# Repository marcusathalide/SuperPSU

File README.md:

This is a replacement power supply unit for the Commodore 64. The unit contains protection elements that shall avoid to damage the C64 during an over-voltage event.

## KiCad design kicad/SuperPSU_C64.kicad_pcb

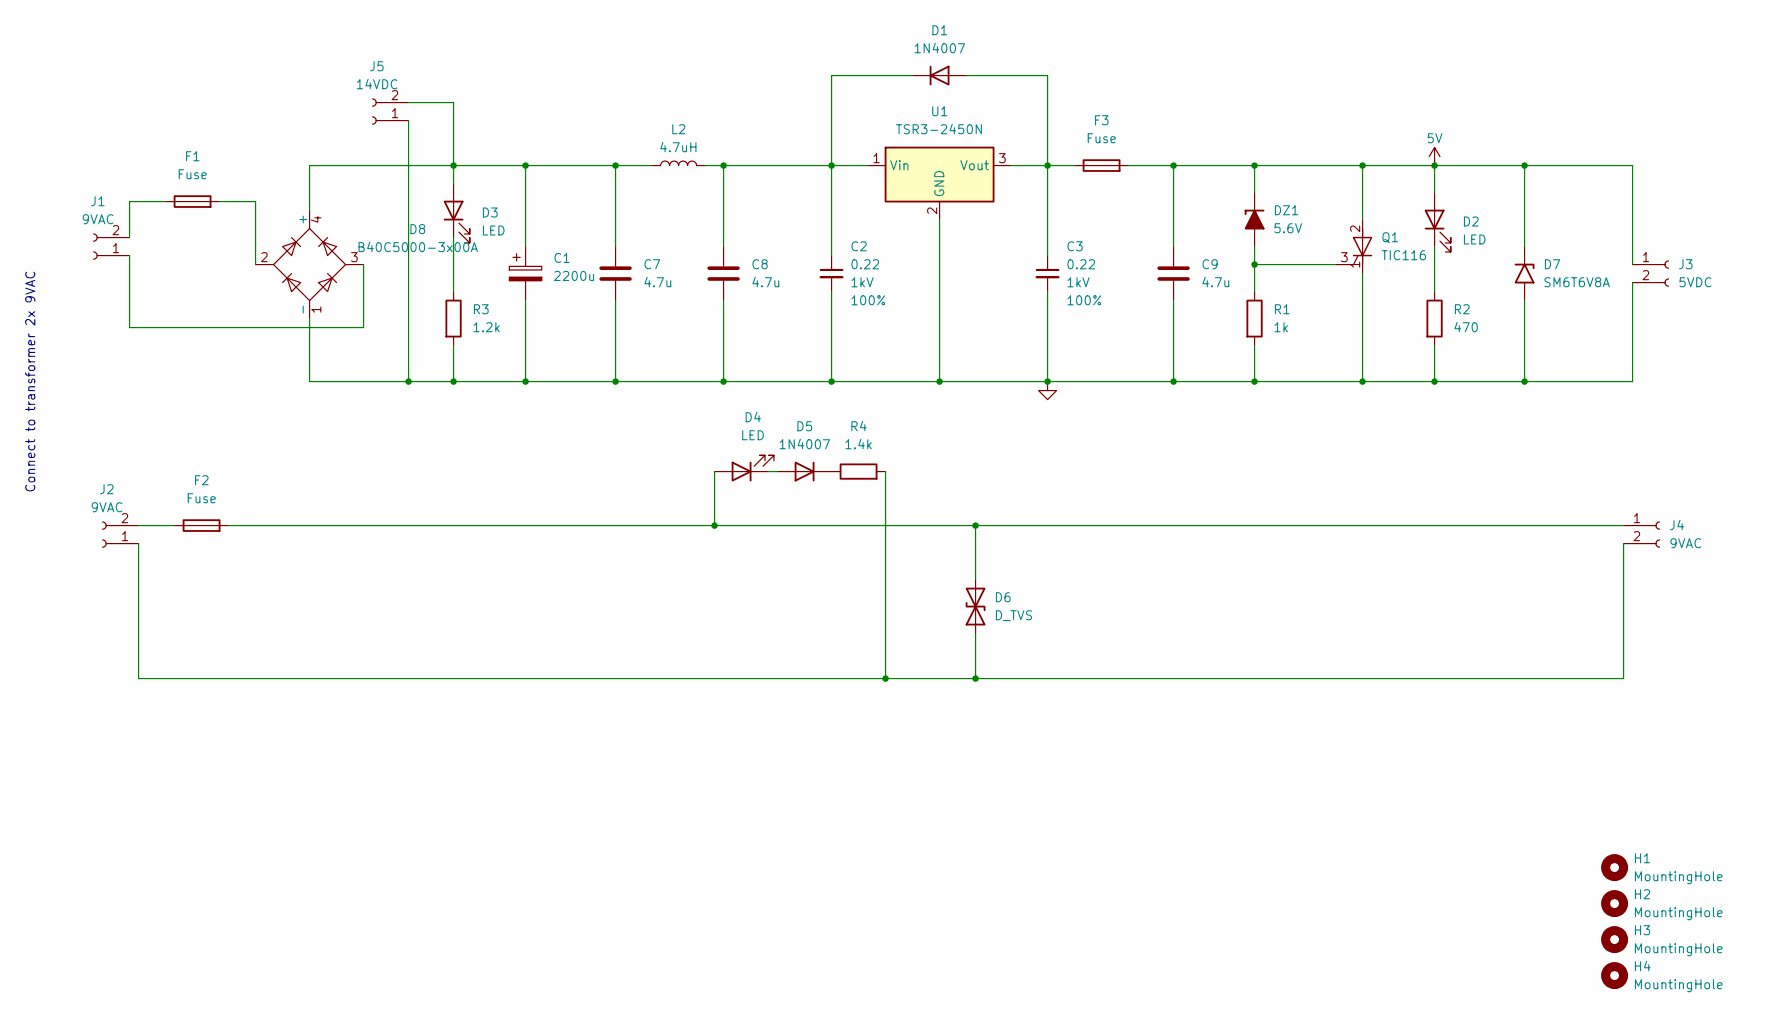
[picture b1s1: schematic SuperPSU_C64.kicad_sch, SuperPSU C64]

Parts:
C1: 2200u; CP_Radial_D16.0mm_P7.50mm
C2, C3: 0.22; C_Disc_D3.0mm_W2.0mm_P2.50mm; Voltage 1kV; Tolerance 100%
C7, C8, C9: 4.7u; CP_Radial_D6.3mm_P2.50mm
D1, D5: 1N4007; D_DO-41_SOD81_P10.16mm_Horizontal
D2, D3, D4: LED; LED_D5.0mm
D6: D_TVS; D_DO-41_SOD81_P10.16mm_Horizontal
D7: SM6T6V8A; D_5W_P10.16mm_Horizontal
D8: B40C5000-3x00A; Diode_Bridge_32.0x5.6x17.0mm_P10.0mm_P7.5mm
DZ1: 5.6V; D_5W_P10.16mm_Horizontal
F1, F2, F3: Fuse; Fuseholder_Littelfuse_445_030_series_5x20mm
H1, H2, H3, H4: MountingHole; MountingHole_3.2mm_M3_DIN965
J1, J2, J4: 9VAC; SolderWire-0.75sqmm_1x02_P7mm_D1.25mm_OD3.5mm
J3: 5VDC; SolderWire-0.75sqmm_1x02_P7mm_D1.25mm_OD3.5mm
J5: 14VDC; SolderWire-0.75sqmm_1x02_P7mm_D1.25mm_OD3.5mm
L2: 4.7uH; L_Bourns_SRP5030T
Q1: TIC116; TO-220-3_Vertical
R1: 1k; R_Axial_DIN0207_L6.3mm_D2.5mm_P10.16mm_Horizontal
R2: 470; R_Axial_DIN0207_L6.3mm_D2.5mm_P10.16mm_Horizontal
R3: 1.2k; R_Axial_DIN0207_L6.3mm_D2.5mm_P10.16mm_Horizontal
R4: 1.4k; R_Axial_DIN0207_L6.3mm_D2.5mm_P10.16mm_Horizontal
U1: TSR3-2450N; Converter_DCDC_TRACO_TSR2-24xxN_TSR2-24xxxN_THT

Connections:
5V: C9.1, D2.2 (A), D7.1 (A1), DZ1.1 (K), F3.2, J3.1, Q1.2 (A)
GND: C1.2, C2.2, C3.2, C7.2, C8.2, C9.2, D7.2 (A2), D8.1 (-), J3.2, J5.1, Q1.1 (K), R1.2, R2.2, R3.2, U1.2 (GND)
unnamed: C3.1, D1.2 (A), F3.1, U1.3 (Vout)
unnamed: C2.1, C8.1, D1.1 (K), L2.2, U1.1 (Vin)
unnamed: D2.1 (K), R2.1
unnamed: C1.1, C7.1, D3.2 (A), D8.4 (+), J5.2, L2.1
unnamed: D3.1 (K), R3.1
unnamed: D4.2 (A), D6.2 (A2), F2.2, J4.1
unnamed: D4.1 (K), D5.2 (A)
unnamed: D5.1 (K), R4.1
unnamed: D6.1 (A1), J2.1, J4.2, R4.2
unnamed: D8.2, F1.2
unnamed: DZ1.2 (A), Q1.3 (G), R1.1
unnamed: D8.3, J1.1
unnamed: F1.1, J1.2
unnamed: F2.1, J2.2

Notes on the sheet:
Connect to transformer 2x 9VAC

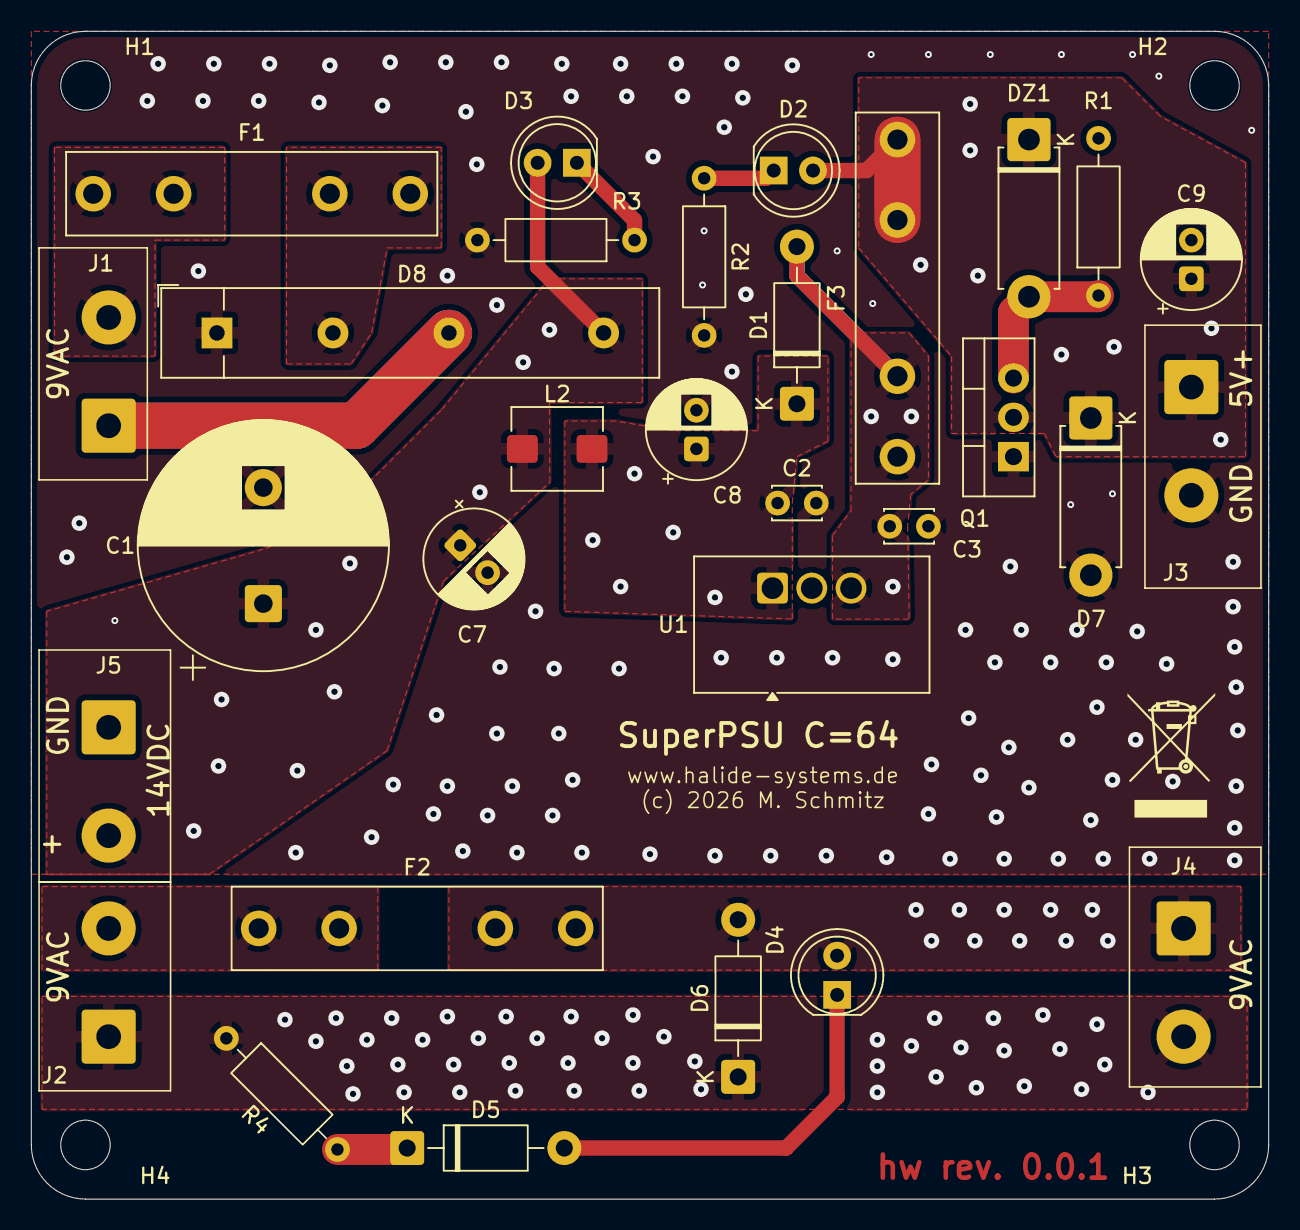
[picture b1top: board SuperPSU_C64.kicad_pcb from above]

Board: 4 copper layers, 80.0 x 75.5 mm, 34 parts (0 on the bottom side), 16 nets.

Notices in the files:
kicad/SuperPSU_C64.kicad_pcb:
(c) 2026 M. Schmitz
